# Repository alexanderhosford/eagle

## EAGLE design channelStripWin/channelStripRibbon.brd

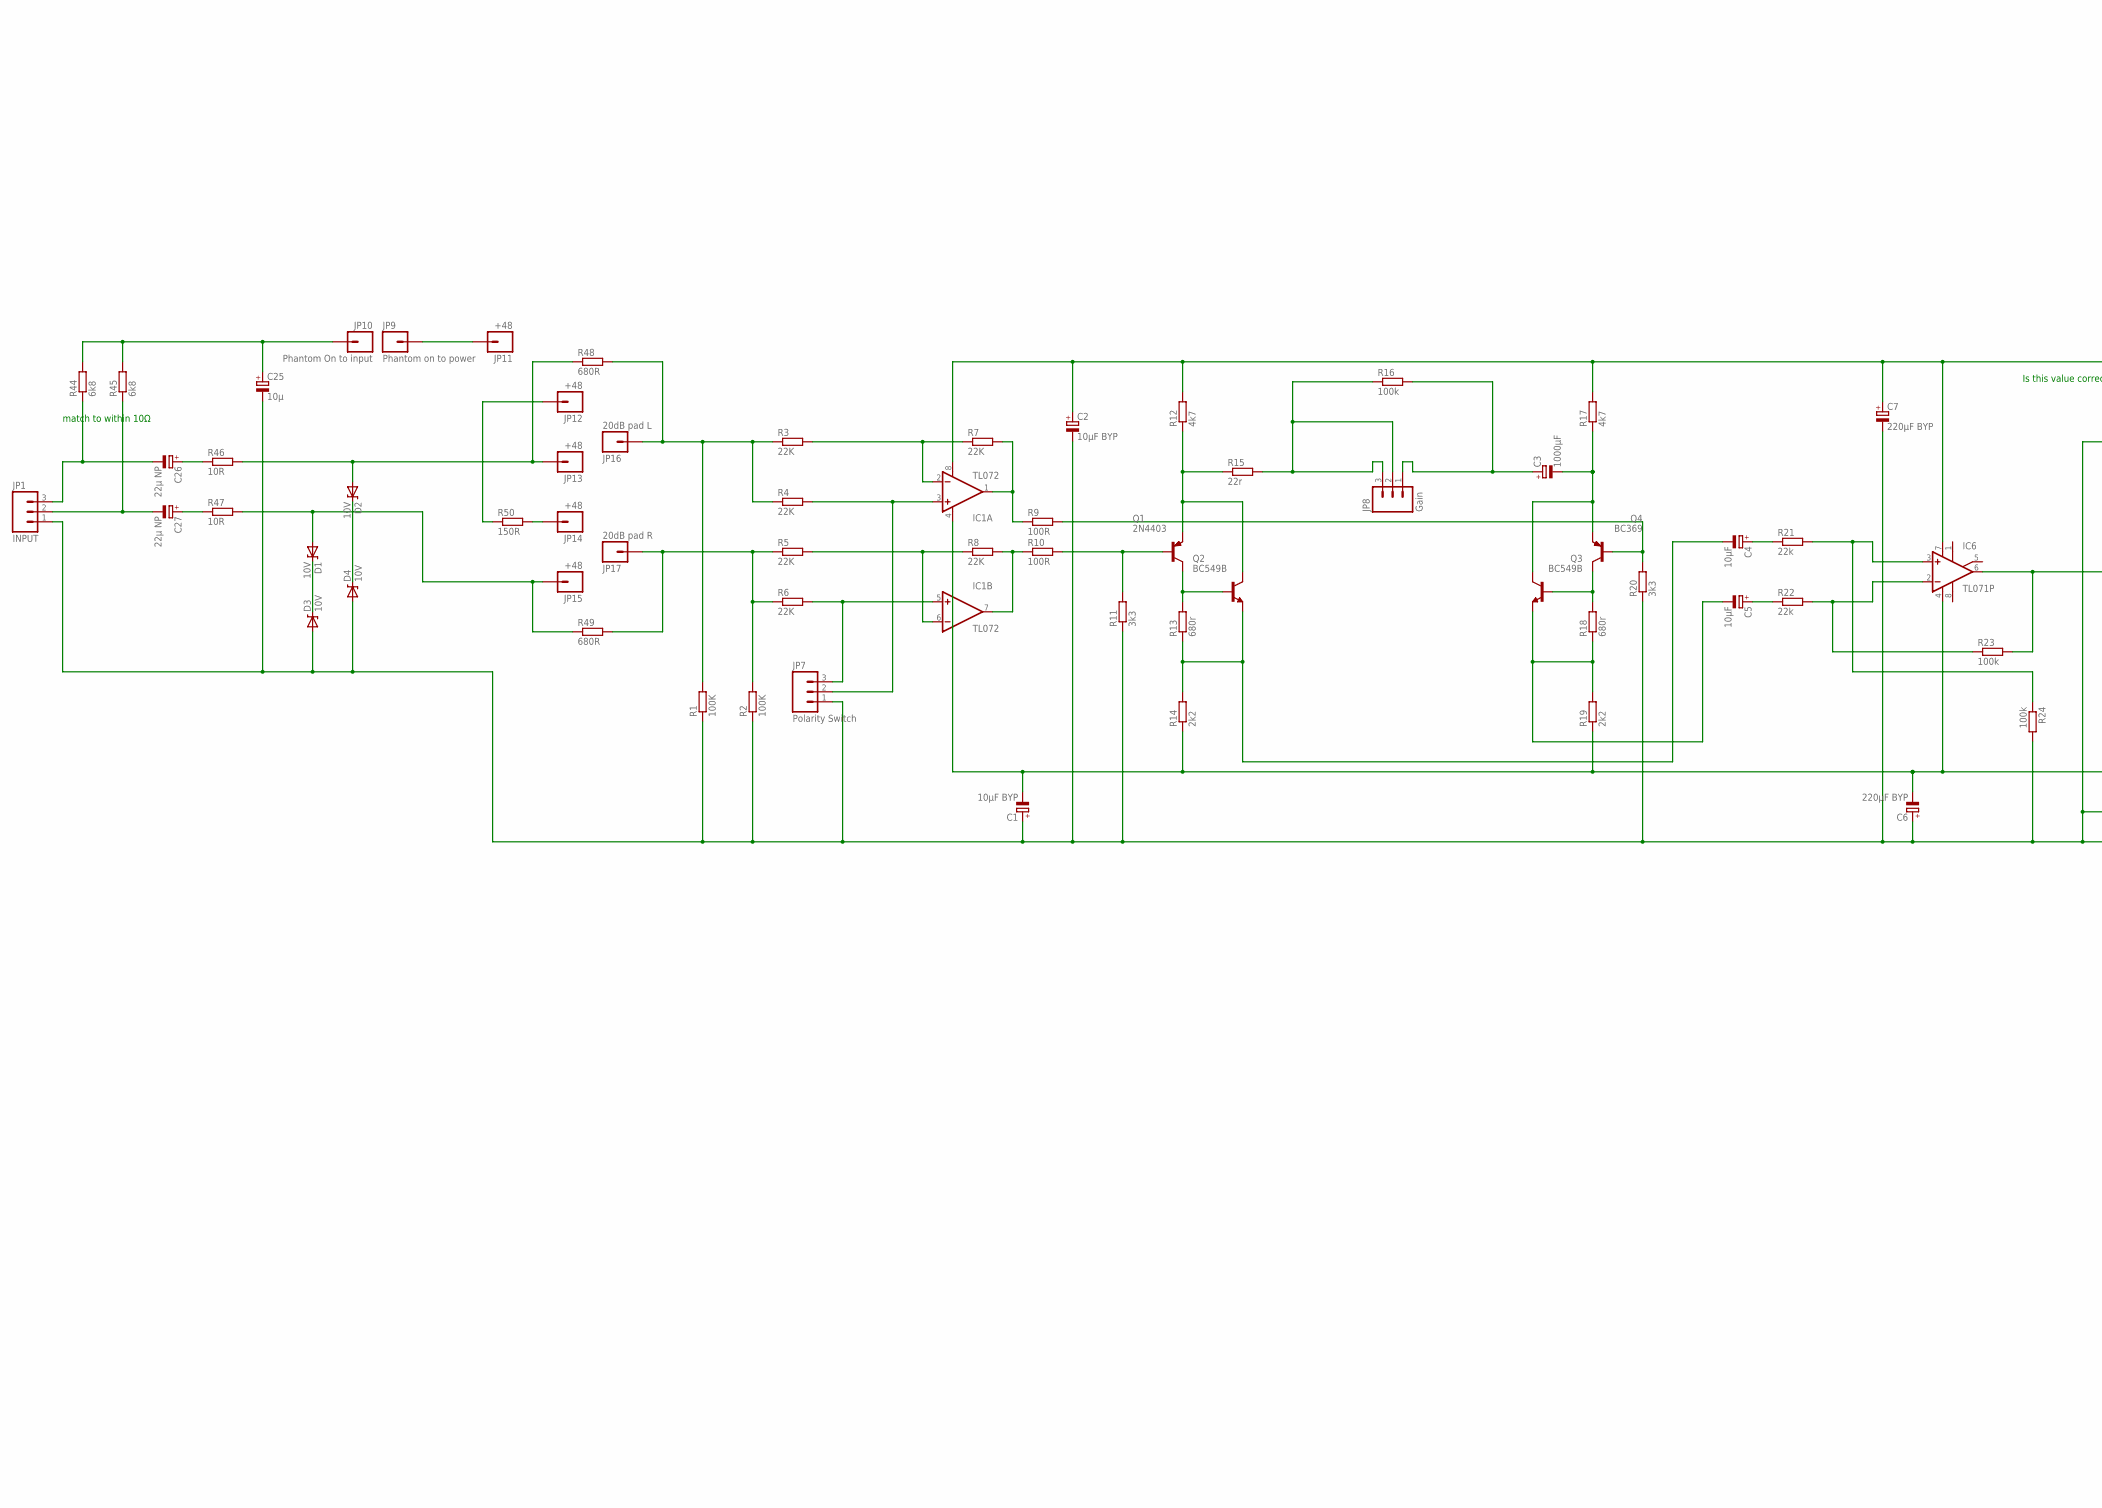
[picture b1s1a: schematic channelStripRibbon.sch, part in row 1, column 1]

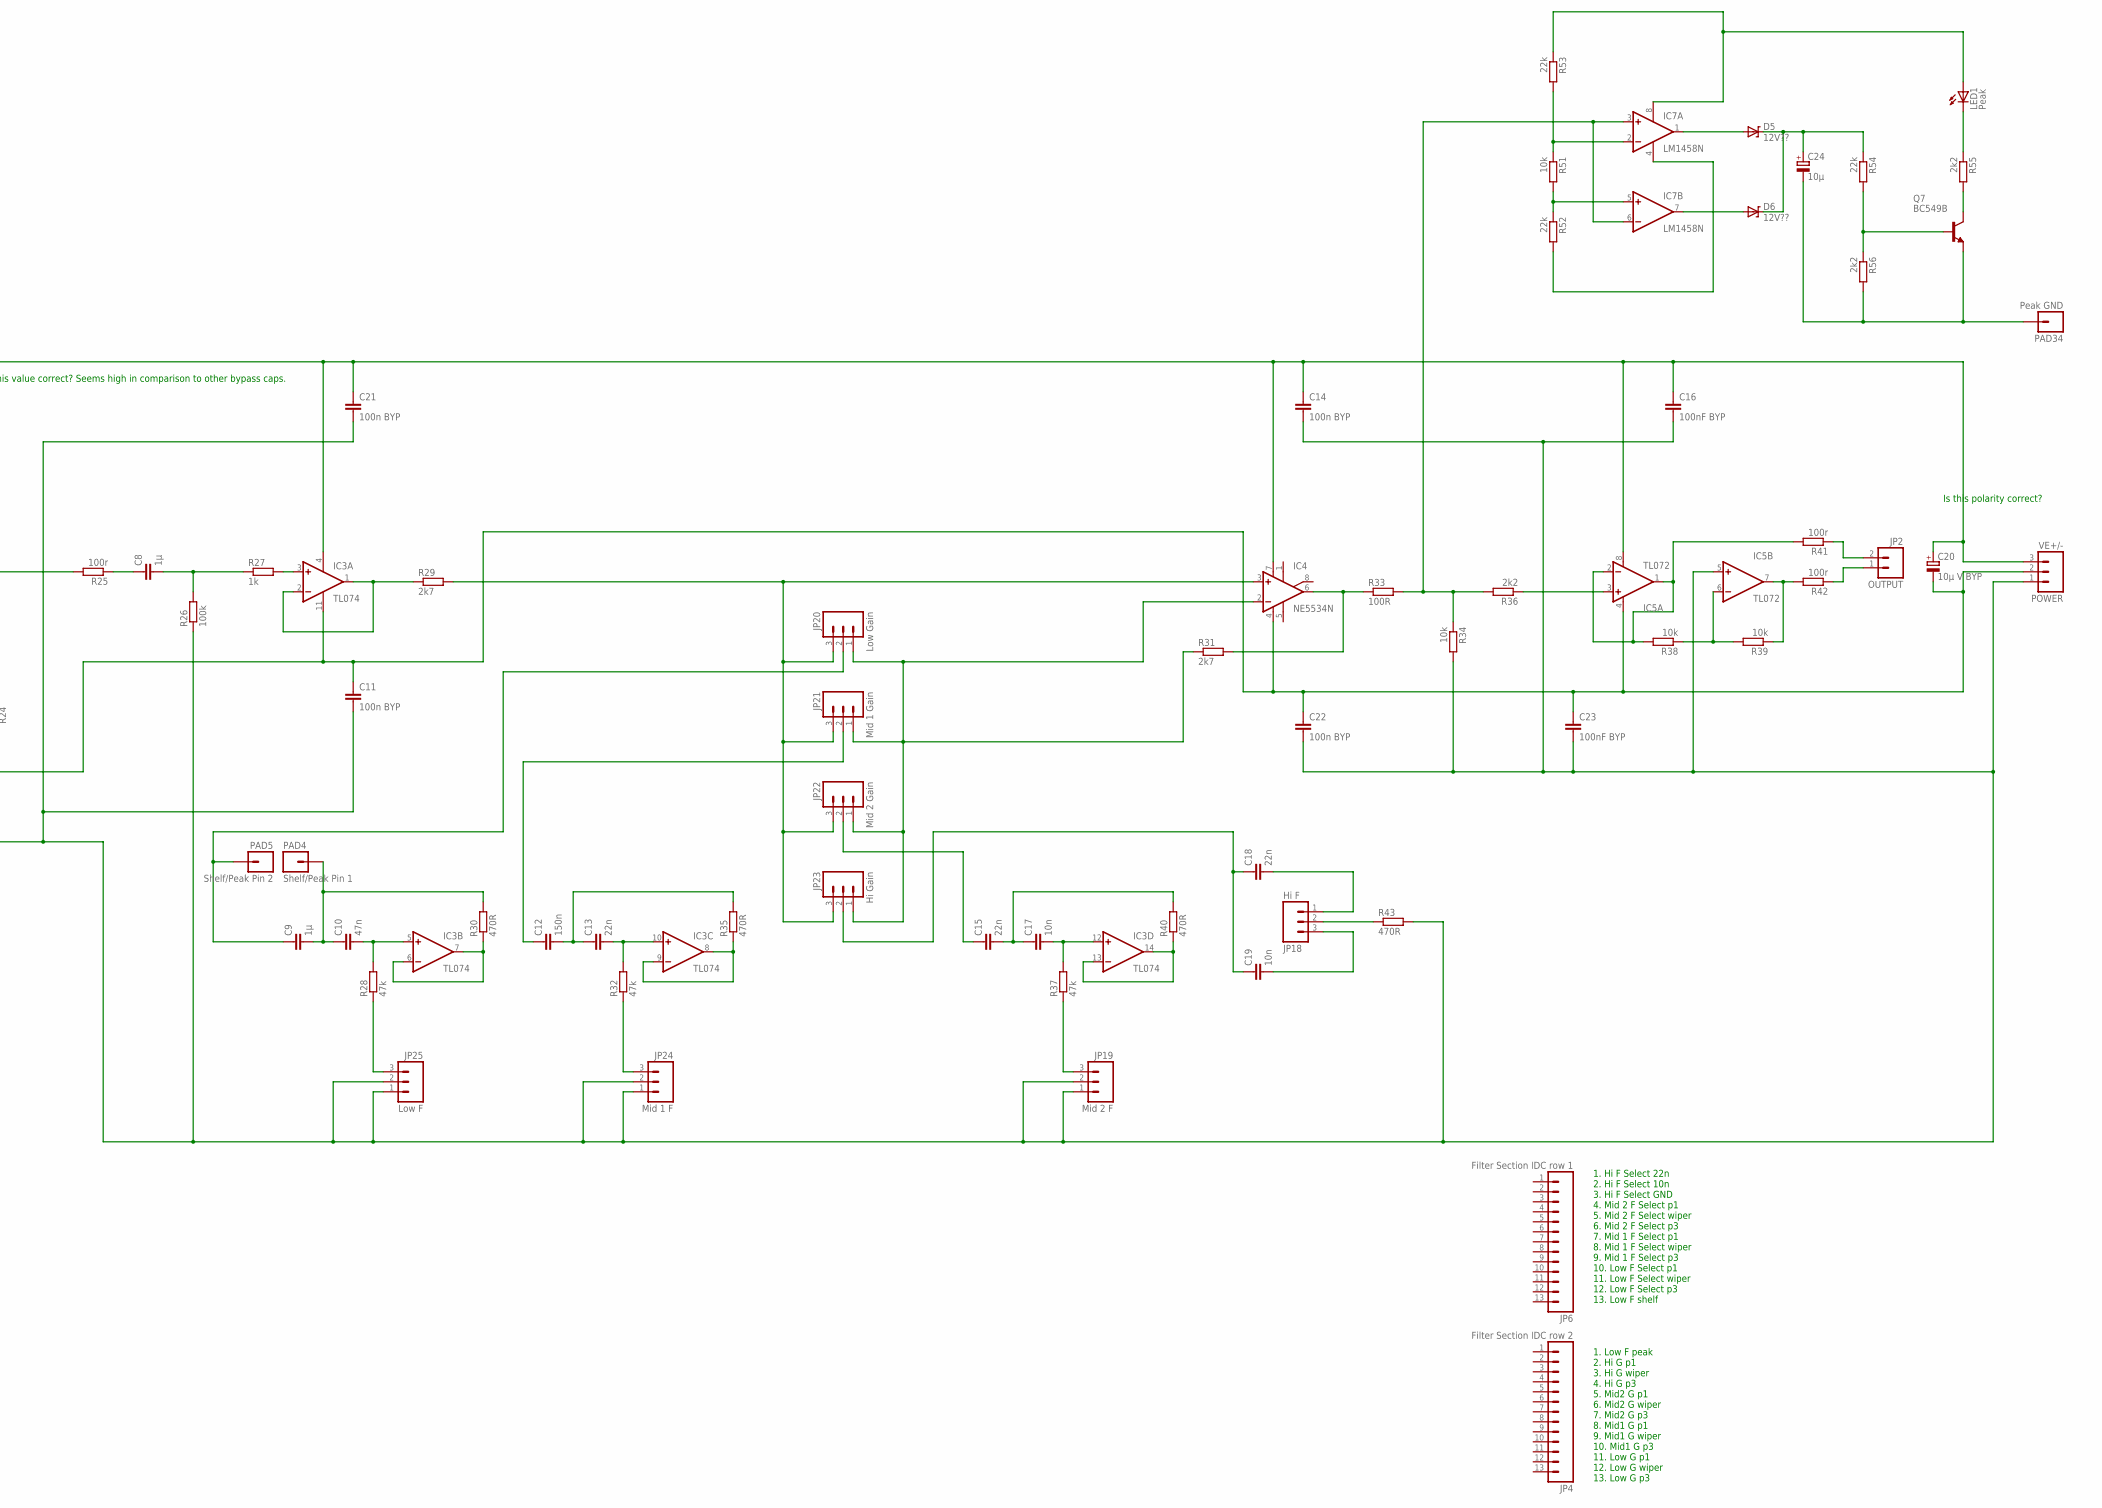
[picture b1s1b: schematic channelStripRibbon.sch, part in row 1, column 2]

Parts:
C1, C2: 10µF BYP; E2,5-6
C3: 1000µF; E5-10,5
C4, C5: 10µF; E15-5
C6, C7: 220µF BYP; E5-10,5
C8, C9: 1µ; C050-025X075
C10: 47n; C050-025X075
C11, C14, C21, C22: 100n BYP; C050-025X075
C12: 150n; C050-025X075
C13, C15, C18: 22n; C050-025X075
C16, C23: 100nF BYP; C050-025X075
C17, C19: 10n; C050-025X075
C20: 10µ V BYP; E2,5-6E
C24: 10µ; E2,5-6E
C25: 10µ; E2,5-6
C26, C27: 22µ NP; E15-5
D1, D2, D3, D4: 10V; DIODE-ZENER
D5, D6: 12V??; DIODE-ZENER
IC1, IC5: TL072; DIP08
IC3: TL074; DIL14
IC4: NE5534N; DIL08
IC6: TL071P; DIL08
IC7: LM1458N; DIL08
JP1: INPUT; SCREWTERMINAL-3.5MM-3
JP2: OUTPUT; SCREWTERMINAL-3.5MM-2
JP4: Filter Section IDC row 2; 1X13
JP6: Filter Section IDC row 1; 1X13
JP7: Polarity Switch; 1X03
JP8: Gain; 1X03
JP9: Phantom on to power; 1X01
JP10: Phantom On to input; 1X01
JP11, JP12, JP13, JP14, JP15: +48; 1X01
JP16: 20dB pad L; 1X01
JP17: 20dB pad R; 1X01
JP18: Hi F; SCREWTERMINAL-3.5MM-3
JP19: Mid 2 F; SCREWTERMINAL-3.5MM-3
JP20: Low Gain; SCREWTERMINAL-3.5MM-3
JP21: Mid 1 Gain; SCREWTERMINAL-3.5MM-3
JP22: Mid 2 Gain; SCREWTERMINAL-3.5MM-3
JP23: Hi Gain; SCREWTERMINAL-3.5MM-3
JP24: Mid 1 F; SCREWTERMINAL-3.5MM-3
JP25: Low F; SCREWTERMINAL-3.5MM-3
LED1: Peak; LED3MM-NS
PAD4: Shelf/Peak Pin 1; 1X01_2MM
PAD5: Shelf/Peak Pin 2; 1X01_2MM
PAD34: Peak GND; 1X01_2MM
Q1: 2N4403; TO92-BCE
Q2, Q3, Q7: BC549B; TO92-EBC
Q4: BC369; TO92-BCE
R1, R2: 100K; 0207/10
R3, R4, R5, R6, R7, R8: 22K; 0207/10
R9, R10, R33: 100R; 0207/10
R11, R20: 3k3; 0207/10
R12, R17: 4k7; 0207/10
R13, R18: 680r; 0207/10
R14, R19, R36, R55, R56: 2k2; 0207/10
R15: 22r; 0207/10
R16, R23, R24, R26: 100k; 0207/10
R21, R22, R52, R53, R54: 22k; 0207/10
R25, R41, R42: 100r; 0207/10
R27: 1k; 0207/10
R28, R32, R37: 47k; 0207/10
R29, R31: 2k7; 0207/10
R30, R35, R40, R43: 470R; 0207/10
R34, R38, R39, R51: 10k; 0207/10
R44, R45: 6k8; 0207/10
R46, R47: 10R; 0207/10
R48, R49: 680R; 0207/10
R50: 150R; 0207/10
VE+/-: POWER; SCREWTERMINAL-3.5MM-3

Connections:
15V+: C2.+, C7.+, C14.1, C16.1, C20.+, C21.1, IC1.8 (V+), IC3.4 (V+), IC4.7 (V+), IC5.8 (V+), IC6.7 (V+), R12.2, R17.2, VE+/-.3
15V-: C1.-, C6.-, C11.1, C20.-, C22.1, C23.1, IC1.4 (V-), IC3.11 (V-), IC4.4 (V-), IC5.4 (V-), IC6.4 (V-), R14.1, R19.1, VE+/-.2
GND: C1.+, C2.-, C6.+, C7.-, C11.2, C14.2, C16.2, C21.2, C22.2, C23.2, C25.-, D3.P$2 (A), D4.P$2 (A), IC5.5 (+IN), JP1.1, JP7.1, JP19.1, JP19.2, JP24.1, JP24.2, JP25.1, JP25.2, R1.1, R2.1, R11.1, R20.1, R24.2, R26.1, R34.2, R43.2, VE+/-.1
unnamed: C15.1, JP22.2
unnamed: IC5.7 (OUT), R39.1, R42.2
unnamed: C4.-, Q2.E, R13.1, R14.2
unnamed: C9.2, C10.1, PAD4.1, R30.2
unnamed: C12.2, C13.1, R35.2
unnamed: C15.2, C17.1, R40.2
unnamed: C19.2, JP18.3
unnamed: C18.2, JP18.1
unnamed: JP18.2, R43.1
unnamed: IC3.13 (-IN), IC3.14 (OUT), R40.1
unnamed: C17.2, IC3.12 (+IN), R37.2
unnamed: JP19.3, R37.1
unnamed: C8.1, R25.1
unnamed: C8.2, R26.2, R27.1
unnamed: IC3.3 (+IN), R27.2
unnamed: IC3.1 (OUT), IC3.2 (-IN), R29.1
unnamed: IC4.2 (-IN), JP20.1, JP21.1, JP22.1, JP23.1, R31.1
unnamed: IC4.6 (OUT), R31.2, R33.1
unnamed: Q7.B, R54.2, R56.1
unnamed: C26.+, R46.1
unnamed: IC3.6 (-IN), IC3.7 (OUT), R30.1
unnamed: C10.2, IC3.5 (+IN), R28.2
unnamed: JP25.3, R28.1
unnamed: C9.1, JP20.2, PAD5.1
unnamed: IC3.8 (OUT), IC3.9 (-IN), R35.1
unnamed: C27.+, R47.1
unnamed: C13.2, IC3.10 (+IN), R32.2
unnamed: JP24.3, R32.1
unnamed: IC7.2 (-IN), R51.1, R53.2
unnamed: C26.-, JP1.3, R44.1
unnamed: C27.-, JP1.2, R45.1
unnamed: C25.+, JP10.1, R44.2, R45.2
unnamed: JP2.1, R42.1
unnamed: JP9.1, JP11.1
unnamed: JP17.1, R2.2, R5.1, R6.1, R49.2
unnamed: JP2.2, R41.1
unnamed: IC6.3 (+IN), R21.2, R24.1
unnamed: IC5.6 (-IN), R38.1, R39.2
unnamed: IC5.1 (OUT), IC5.2 (-IN), R38.2, R41.2
unnamed: IC5.3 (+IN), R36.1
unnamed: C18.1, C19.1, JP23.2
unnamed: C4.+, R21.1
unnamed: IC6.6 (OUT), R23.2, R25.2
unnamed: IC6.2 (-IN), R22.2, R23.1
unnamed: C5.+, R22.1
unnamed: JP8.2, JP8.3, R15.2, R16.1
unnamed: C3.+, JP8.1, R16.2
unnamed: C3.-, Q3.C, Q4.E, R17.1
unnamed: Q1.E, Q2.C, R12.1, R15.1
unnamed: Q3.B, Q4.C, R18.2
unnamed: IC1.1 (OUT), R7.2, R9.1
unnamed: Q1.C, Q2.B, R13.2
unnamed: IC7.5 (+IN), R51.2, R52.1
unnamed: IC1.7 (OUT), R8.2, R10.1
unnamed: C5.-, Q3.E, R18.1, R19.2
unnamed: Q4.B, R9.2, R20.2
unnamed: Q1.B, R10.2, R11.2
unnamed: IC1.6 (-IN), R5.2, R8.1
unnamed: D2.P$1 (C), D4.P$1 (C)
unnamed: IC1.2 (-IN), R3.2, R7.1
unnamed: IC1.5 (+IN), JP7.3, R6.2
unnamed: IC1.3 (+IN), JP7.2, R4.2
unnamed: JP16.1, R1.2, R3.1, R4.1, R48.2
unnamed: D1.P$1 (C), D3.P$1 (C)
unnamed: Q7.C, R55.2
unnamed: JP14.1, R50.2
unnamed: JP12.1, R50.1
unnamed: D1.P$2 (A), JP15.1, R47.2, R49.1
unnamed: C24.+, D5.P$1 (C), D6.P$1 (C), R54.1
unnamed: LED1.K (C), R55.1
unnamed: D5.P$2 (A), IC7.1 (OUT)
unnamed: D6.P$2 (A), IC7.7 (OUT)
unnamed: D2.P$2 (A), JP13.1, R46.2, R48.1
unnamed: IC7.3 (+IN), IC7.6 (-IN), R33.2, R34.1, R36.2
unnamed: IC7.4 (V-), R52.2
unnamed: IC7.8 (V+), LED1.A, R53.1
unnamed: IC4.3 (+IN), JP20.3, JP21.3, JP22.3, JP23.3, R29.2
unnamed: C12.1, JP21.2
PEAKGND: C24.-, PAD34.1, Q7.E, R56.2

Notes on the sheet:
Is this polarity correct?
Is this value correct? Seems high in comparison to other bypass caps.
match to within 10Ω
1. Hi F Select 22n 2. Hi F Select 10n 3. Hi F Select GND 4. Mid 2 F Select p1 5. Mid 2 F Select wiper 6. Mid 2 F Select p3 7. Mid 1 F Select p1 8. Mid 1 F Select wiper 9. Mid 1 F Select p3 10. Low F Select p1 11. Low F Select wiper 12. Low F Select p3 13. Low F shelf 1. Low F peak 2. Hi G p1 3. Hi 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

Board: 2 copper layers, 128 parts (0 on the bottom side), 82 nets, no tracks yet.

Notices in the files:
parts and their libraries:
SparkFun: Licensing: CC v3.0 Share-Alike You are welcome to use this library for commercial purposes.
